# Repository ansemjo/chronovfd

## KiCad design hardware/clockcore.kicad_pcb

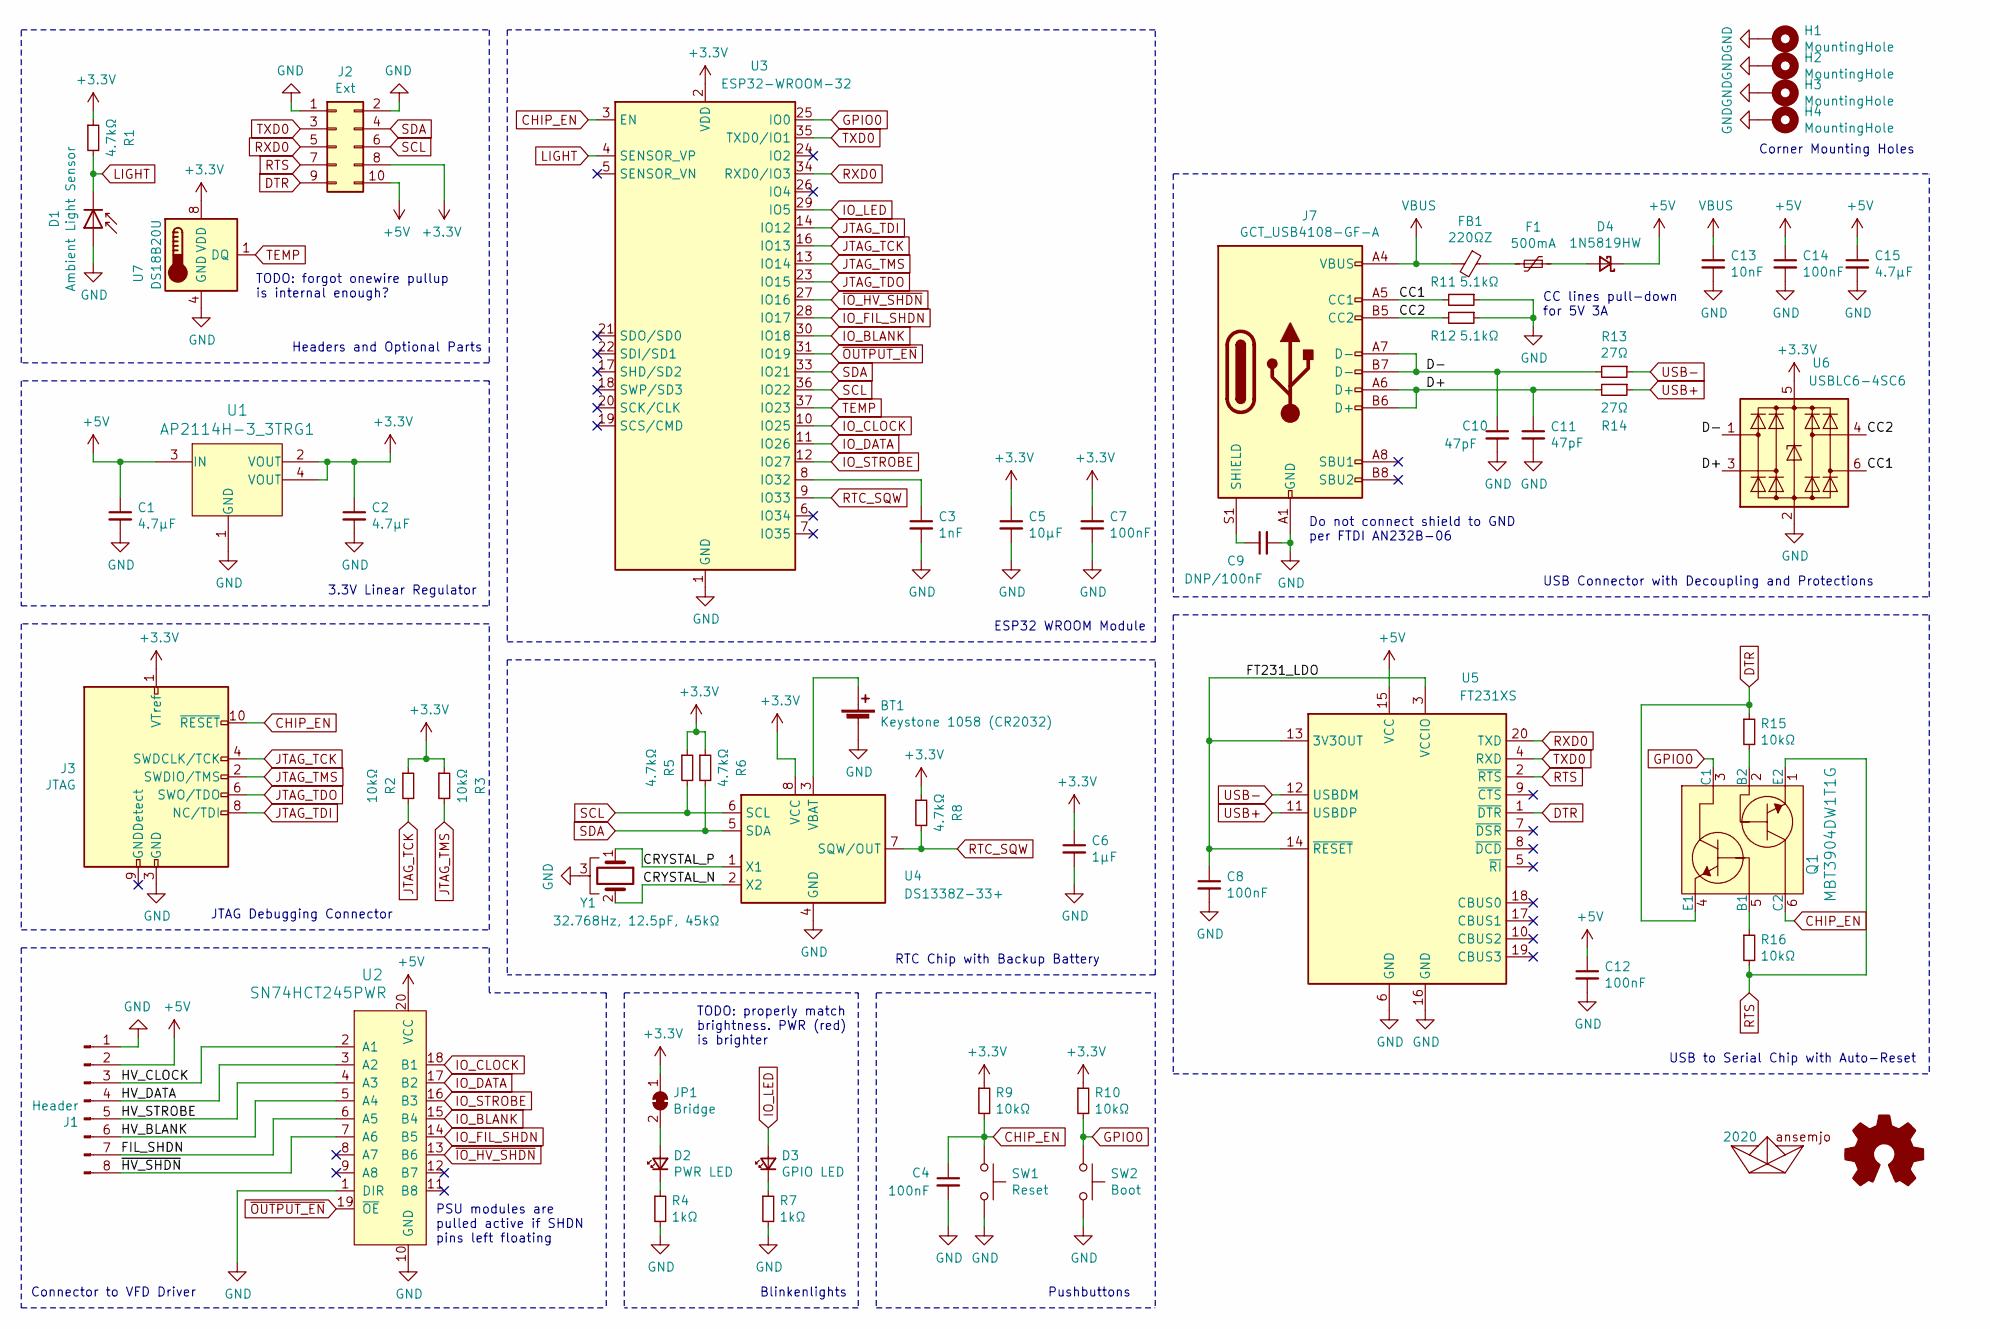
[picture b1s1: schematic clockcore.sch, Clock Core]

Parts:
A1: 2020; AHOI
A2: Logo_Open_Hardware_Small; OSHW-Symbol_6.7x6mm_SilkScreen
BT1: Keystone 1058 (CR2032); BatteryHolder_Keystone_1058_1x2032; MPN 1058; Digi-Key_PN 36-1058-ND
C1, C2, C15: 4.7µF; C_0805_2012Metric_Pad1.15x1.40mm_HandSolder; MPN CL21A475KAQNNNE; Digi-Key_PN 1276-1244-1-ND
C3: 1nF; C_0805_2012Metric_Pad1.15x1.40mm_HandSolder; MPN CL21B102KBANNNC; Digi-Key_PN 1276-1020-1-ND
C4, C7, C8, C12, C14: 100nF; C_0805_2012Metric_Pad1.15x1.40mm_HandSolder; MPN CL21B104KACNNNC; Digi-Key_PN 1276-1099-1-ND
C5: 10µF; C_0805_2012Metric_Pad1.15x1.40mm_HandSolder; MPN CL21A106KOQNNNE; Digi-Key_PN 1276-1096-1-ND
C6: 1µF; C_0805_2012Metric_Pad1.15x1.40mm_HandSolder; MPN CL21B105KAFNNNG; Digi-Key_PN 1276-6469-1-ND
C9: DNP/100nF; C_0805_2012Metric_Pad1.15x1.40mm_HandSolder; MPN CL21B104KACNNNC; Digi-Key_PN 1276-1099-1-ND
C10, C11: 47pF; C_0805_2012Metric_Pad1.15x1.40mm_HandSolder; MPN CC0805JRNPO9BN470; Digi-Key_PN 311-1107-1-ND
C13: 10nF; C_0805_2012Metric_Pad1.15x1.40mm_HandSolder; MPN CC0805KRX7R9BB103; Digi-Key_PN 311-1136-1-ND
D1: Ambient Light Sensor; D_1206_3216Metric_Castellated; MPN VEMD1060X01; Digi-Key_PN VEMD1060X01CT-ND
D2: PWR LED; LED_0805_2012Metric_Pad1.15x1.40mm_HandSolder; MPN 150080SS75000; Digi-Key_PN 732-4985-1-ND
D3: GPIO LED; LED_0805_2012Metric_Pad1.15x1.40mm_HandSolder; MPN 150080VS75000; Digi-Key_PN 732-4986-1-ND
D4: 1N5819HW; D_SOD-123; MPN 1N5819HW-7-F; Digi-Key_PN 1N5819HW-FDICT-ND
F1: 500mA; Fuse_1206_3216Metric_Pad1.42x1.75mm_HandSolder; MPN 0ZCJ0050FF2G; Digi-Key_PN 507-1802-1-ND
FB1: 220ΩZ; L_0805_2012Metric_Pad1.15x1.40mm_HandSolder; MPN BLM21PG221SZ1D; Digi-Key_PN 490-16661-1-ND
H1, H2, H3, H4: MountingHole; MountingHole_2.7mm_M2.5_Pad
J1: Header; PinSocket_1x08_P2.54mm_Vertical; MPN PPTC081LFBN-RC; Digi-Key_PN S7006-ND
J2: Ext; PinHeader_2x05_P2.54mm_Vertical; MPN PRPC040DAAN-RC; Digi-Key_PN S2011EC-40-ND
J3: JTAG; JTAG_2x05_P1.27mm_Vertical_SMD; MPN 20021121-00010C4LF; Digi-Key_PN 609-3695-6-ND
J7: GCT_USB4108-GF-A; USB_C_Receptacle_HRO_TYPE-C-31-M-12; MPN USB4105-GF-A; Digi-Key_PN 2073-USB4105-GF-ACT-ND
JP1: Bridge; SolderJumper-2_P1.3mm_Bridged_RoundedPad1.0x1.5mm
Q1: MBT3904DW1T1G; SOT-363; MPN MBT3904DW1T1G; Digi-Key_PN MBT3904DW1T1GOSCT-ND
R1, R5, R6, R8: 4.7kΩ; R_0805_2012Metric_Pad1.15x1.40mm_HandSolder; MPN RC0805FR-074K7L; Digi-Key_PN 311-4.70KCRCT-ND
R2, R3, R9, R10, R15, R16: 10kΩ; R_0805_2012Metric_Pad1.15x1.40mm_HandSolder; MPN RC0805FR-0710KL; Digi-Key_PN 311-10.0KCRCT-ND
R4, R7: 1kΩ; R_0805_2012Metric_Pad1.15x1.40mm_HandSolder; MPN RC0805FR-071KL; Digi-Key_PN 311-1.00KCRCT-ND
R11, R12: 5.1kΩ; R_0805_2012Metric_Pad1.15x1.40mm_HandSolder; MPN RC0805JR-075K1L; Digi-Key_PN 311-5.1KARCT-ND
R13, R14: 27Ω; R_0805_2012Metric_Pad1.15x1.40mm_HandSolder; MPN RC0805FR-0727RL; Digi-Key_PN 311-27.0CRCT-ND
SW1: Reset; SW_PTS526_SM08_SMTR2_LFS; MPN PTS526 SK15 SMTR2 LFS; Digi-Key_PN CKN12221-1-ND
SW2: Boot; SW_PTS526_SM08_SMTR2_LFS; MPN PTS526 SK15 SMTR2 LFS; Digi-Key_PN CKN12221-1-ND
U1: AP2114H-3_3TRG1; SOT-223; MPN AP2114H-3.3TRG1; Digi-Key_PN AP2114H-3.3TRG1DICT-ND
U2: ‎SN74HCT245PWR‎; TSSOP-20_4.4x6.5mm_P0.65mm; MPN SN74HCT245PWR; Digi-Key_PN 296-8404-1-ND
U3: ESP32-WROOM-32; MPN ESP32-WROOM-32E (8MB); Digi-Key_PN 1965-ESP32-WROOM-32E(8MBFLASH)CT-ND
U4: DS1338Z-33+; SOIC-8_3.9x4.9mm_P1.27mm; MPN DS1338Z-33+T&R; Digi-Key_PN DS1338Z-33+T&RCT-ND
U5: FT231XS; SSOP-20_3.9x8.7mm_P0.635mm; MPN FT231XS-R; Digi-Key_PN 768-1129-1-ND
U6: USBLC6-4SC6; SOT-23-6; MPN USBLC6-4SC6; Digi-Key_PN 497-4492-1-ND
U7: DS18B20U; MSOP-8_3x3mm_P0.65mm; MPN DS18B20U+T&R; Digi-Key_PN DS18B20U+T&RCT-ND
Y1: 32.768Hz, 12.5pF, 45kΩ; Crystal_SMD_MicroCrystal_MS1V-T1K; MPN ECS-.327-12.5-13FLX-C; Digi-Key_PN XC1911CT-ND

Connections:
+3V3: C2.1, C5.1, C6.1, C7.1, J2.8, J3.1 (VTref), JP1.1 (A), R1.1, R2.1, R3.1, R5.1, R6.1, R8.1, R9.1, R10.1, U1.2 (VOUT), U1.4 (VOUT), U3.2 (VDD), U4.8 (VCC), U6.5 (VBUS), U7.8 (VDD)
+5V: C1.1, C12.1, C14.1, C15.1, D4.1 (K), J1.2, J2.10, U1.3 (IN), U2.20 (VCC), U5.15 (VCC)
/CC1: J7.A5 (CC1), R11.2, U6.6 (I/O4)
/CC2: J7.B5 (CC2), R12.2, U6.4 (I/O3)
/CRYSTAL_N: U4.2 (X2), Y1.2
/CRYSTAL_P: U4.1 (X1), Y1.1
/D+: C11.1, J7.A6 (D+), J7.B6 (D+), R14.2, U6.3 (I/O2)
/D-: C10.1, J7.A7 (D-), J7.B7 (D-), R13.2, U6.1 (I/O1)
/FIL_SHDN: J1.7, U2.6 (A5)
/FT231_LDO: C8.1, U5.3 (VCCIO), U5.13 (3V3OUT), U5.14 (~RESET)
/HV_BLANK: J1.6, U2.5 (A4)
/HV_CLOCK: J1.3, U2.2 (A1)
/HV_DATA: J1.4, U2.3 (A2)
/HV_STROBE: J1.5, U2.4 (A3)
/~HV_SHDN~: J1.8, U2.7 (A6)
CHIP_EN: C4.1, J3.10 (~RESET~), Q1.6 (C2), R9.2, SW1.1, U3.3 (EN)
DTR: J2.9, Q1.4 (E1), R15.1, U5.1 (~DTR)
GND: BT1.2 (-), C1.2, C2.2, C3.2, C4.2, C5.2, C6.2, C7.2, C8.2, C9.2, C10.2, C11.2, C12.2, C13.2, C14.2, C15.2, D1.2 (A), H1.1, H2.1, H3.1, H4.1, J1.1, J2.1, J2.2, J3.3 (GND), J3.5 (GND), J7.A1 (GND), J7.A12 (GND), J7.B1 (GND), J7.B12 (GND), R4.2, R7.2, R11.1, R12.1, SW1.2, SW2.2, U1.1 (GND), U2.1 (DIR), U2.10 (GND), U3.1 (GND), U3.15 (GND), U3.38 (GND), U3.39 (GND), U4.4 (GND), U5.6 (GND), U5.16 (GND), U6.2 (GND), U7.4 (GND), Y1.3
GPIO0: Q1.3 (C1), R10.2, SW2.1, U3.25 (IO0)
IO_BLANK: U2.15 (B4), U3.30 (IO18)
IO_CLOCK: U2.18 (B1), U3.10 (IO25)
IO_DATA: U2.17 (B2), U3.11 (IO26)
IO_FIL_SHDN: U2.14 (B5), U3.28 (IO17)
IO_LED: D3.2 (A), U3.29 (IO5)
IO_STROBE: U2.16 (B3), U3.12 (IO27)
JTAG_TCK: J3.4 (SWDCLK/TCK), R2.2, U3.16 (IO13)
JTAG_TDI: J3.8 (NC/TDI), U3.14 (IO12)
JTAG_TDO: J3.6 (SWO/TDO), U3.23 (IO15)
JTAG_TMS: J3.2 (SWDIO/TMS), R3.2, U3.13 (IO14)
LIGHT: D1.1 (K), R1.2, U3.4 (SENSOR_VP)
unnamed: BT1.1 (+), U4.3 (VBAT)
unnamed: C3.1, U3.8 (IO32)
unnamed: C9.1, J7.S1 (SHIELD)
unnamed: D2.1 (K), R4.1
unnamed: D2.2 (A), JP1.2 (B)
unnamed: D3.1 (K), R7.1
unnamed: D4.2 (A), F1.1
unnamed: F1.2, FB1.1
unnamed: Q1.2 (B2), R15.2
unnamed: Q1.5 (B1), R16.1
RTC_SQW: R8.2, U3.9 (IO33), U4.7 (SQW/OUT)
RTS: J2.7, Q1.1 (E2), R16.2, U5.2 (~RTS)
RXD0: J2.5, U3.34 (RXD0/IO3), U5.20 (TXD)
SCL: J2.6, R5.2, U3.36 (IO22), U4.6 (SCL)
SDA: J2.4, R6.2, U3.33 (IO21), U4.5 (SDA)
TEMP: U3.37 (IO23), U7.1 (DQ)
TXD0: J2.3, U3.35 (TXD0/IO1), U5.4 (RXD)
USB+: R14.1, U5.11 (USBDP)
USB-: R13.1, U5.12 (USBDM)
VBUS: C13.1, FB1.2, J7.A4 (VBUS), J7.A9 (VBUS), J7.B4 (VBUS), J7.B9 (VBUS)
~IO_HV_SHDN~: U2.13 (B6), U3.27 (IO16)
~OUTPUT_EN~: U2.19 (~OE), U3.31 (IO19)

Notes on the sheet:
CC lines pull-down for 5V 3A
PSU modules are pulled active if SHDN pins left floating
RTC Chip with Backup Battery
USB Connector with Decoupling and Protections
USB to Serial Chip with Auto-Reset
Connector to VFD Driver
Blinkenlights
Pushbuttons
Corner Mounting Holes
Do not connect shield to GND per FTDI AN232B-06
JTAG Debugging Connector
3.3V Linear Regulator
Headers and Optional Parts
ESP32 WROOM Module
TODO: forgot onewire pullup is internal enough?
TODO: properly match brightness. PWR (red) is brighter

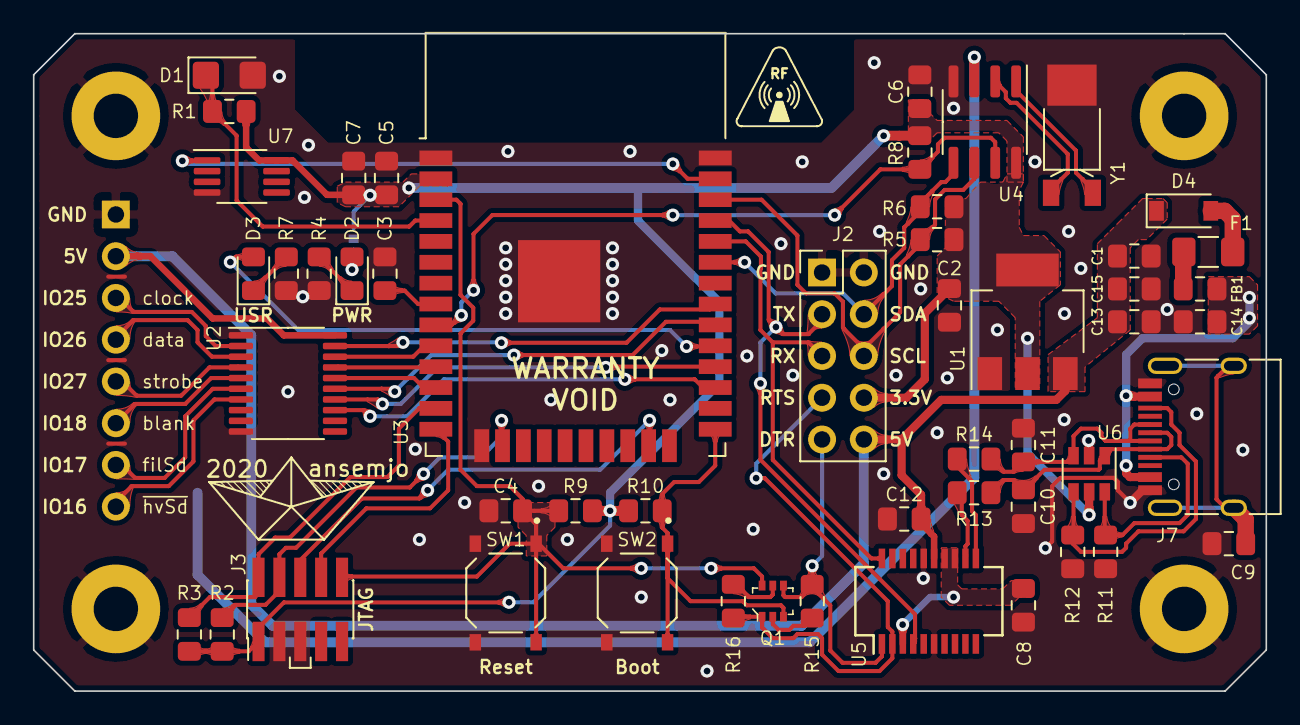
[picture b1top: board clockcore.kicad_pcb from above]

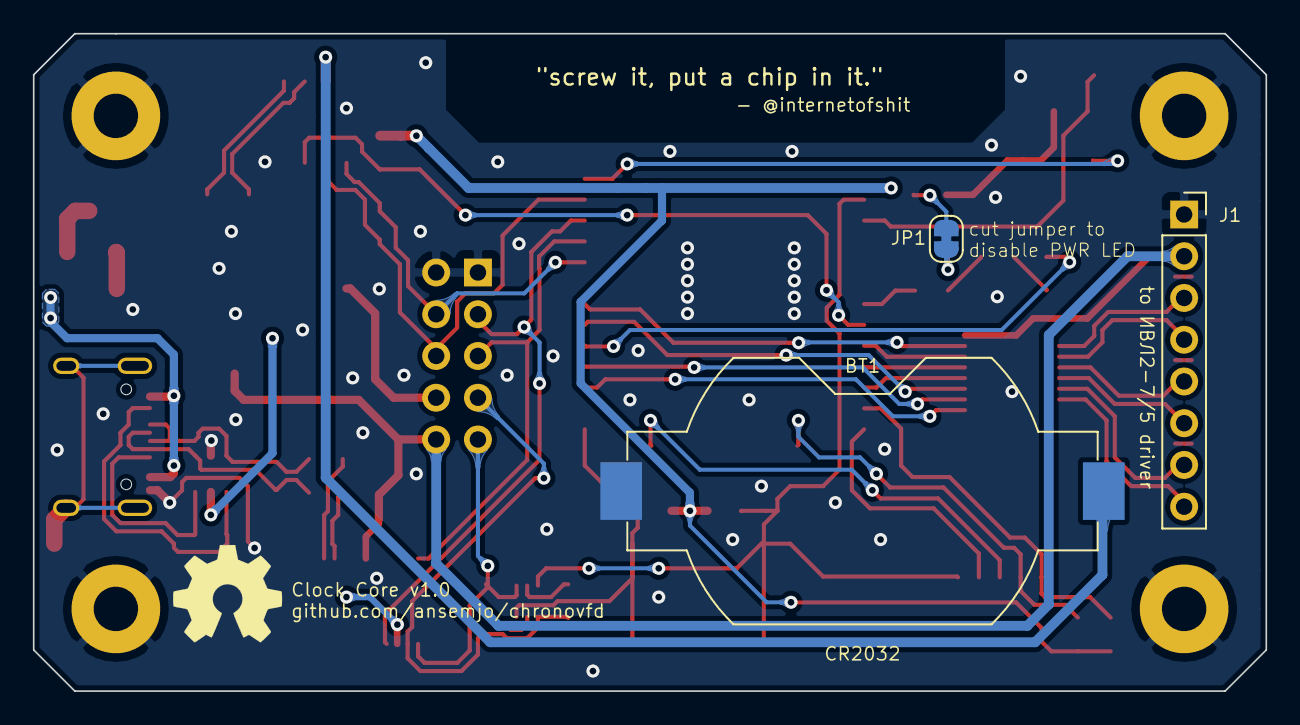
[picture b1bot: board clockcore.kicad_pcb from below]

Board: 2 copper layers, 75.0 x 40.0 mm, 60 parts (4 on the bottom side), 52 nets.

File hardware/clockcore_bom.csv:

References,Value,Footprint,Quantity,Digi-Key PN,Manufacturer,MPN
BT1,Keystone 1058 (CR2032),BatteryHolder_Keystone_1058_1x2032,1,36-1058-ND,Keystone,1058
C4 C7 C8 C12 C14,100nF,C_0805_2012Metric_Pad1.15x1.40mm_HandSolder,5,1276-1099-1-ND,Samsung,CL21B104KACNNNC
C13,10nF,C_0805_2012Metric_Pad1.15x1.40mm_HandSolder,1,311-1136-1-ND,Yageo,CC0805KRX7R9BB103
C5,10µF,C_0805_2012Metric_Pad1.15x1.40mm_HandSolder,1,1276-1096-1-ND,Samsung,CL21A106KOQNNNE
C3,1nF,C_0805_2012Metric_Pad1.15x1.40mm_HandSolder,1,1276-1020-1-ND,Samsung,CL21B102KBANNNC
C6,1µF,C_0805_2012Metric_Pad1.15x1.40mm_HandSolder,1,1276-6469-1-ND,Samsung,CL21B105KAFNNNG
C1 C2 C15,4.7µF,C_0805_2012Metric_Pad1.15x1.40mm_HandSolder,3,1276-1244-1-ND,Samsung,CL21A475KAQNNNE
C10 C11,47pF,C_0805_2012Metric_Pad1.15x1.40mm_HandSolder,2,311-1107-1-ND,Yageo,CC0805JRNPO9BN470
C9,DNP/100nF,C_0805_2012Metric_Pad1.15x1.40mm_HandSolder,1,1276-1099-1-ND,Samsung,CL21B104KACNNNC
D4,1N5819HW,D_SOD-123,1,1N5819HW-FDICT-ND,Diodes Inc.,1N5819HW-7-F
D1,Ambient Light Sensor,D_1206_3216Metric_Castellated,1,VEMD1060X01CT-ND,Vishay,VEMD1060X01
D3,GPIO LED,LED_0805_2012Metric_Pad1.15x1.40mm_HandSolder,1,732-4986-1-ND,Würth,150080VS75000
D2,PWR LED,LED_0805_2012Metric_Pad1.15x1.40mm_HandSolder,1,732-4985-1-ND,Würth,150080SS75000
F1,500mA,Fuse_1206_3216Metric_Pad1.42x1.75mm_HandSolder,1,507-1802-1-ND,Bel Fuse,0ZCJ0050FF2G
FB1,220ΩZ,L_0805_2012Metric_Pad1.15x1.40mm_HandSolder,1,490-16661-1-ND,Murata,BLM21PG221SZ1D
J2,Ext,PinHeader_2x05_P2.54mm_Vertical,1,S2011EC-40-ND,Sullins,PRPC040DAAN-RC
J7,GCT_USB4108-GF-A,USB_C_Receptacle_HRO_TYPE-C-31-M-12,1,2073-USB4105-GF-ACT-ND,GCT,USB4105-GF-A
J1,Header,PinSocket_1x08_P2.54mm_Vertical,1,S7006-ND,Sullins,PPTC081LFBN-RC
J3,JTAG,JTAG_2x05_P1.27mm_Vertical_SMD,1,609-3695-6-ND,Amphenol,20021121-00010C4LF
Q1,MBT3904DW1T1G,SOT-363,1,MBT3904DW1T1GOSCT-ND,ON Semiconductor,MBT3904DW1T1G
R2 R3 R9 R10 R15 R16,10kΩ,R_0805_2012Metric_Pad1.15x1.40mm_HandSolder,6,311-10.0KCRCT-ND,Yageo,RC0805FR-0710KL
R4 R7,1kΩ,R_0805_2012Metric_Pad1.15x1.40mm_HandSolder,2,311-1.00KCRCT-ND,Yageo,RC0805FR-071KL
R13 R14,27Ω,R_0805_2012Metric_Pad1.15x1.40mm_HandSolder,2,311-27.0CRCT-ND,Yageo,RC0805FR-0727RL
R1 R5 R6 R8,4.7kΩ,R_0805_2012Metric_Pad1.15x1.40mm_HandSolder,4,311-4.70KCRCT-ND,Yageo,RC0805FR-074K7L
R11 R12,5.1kΩ,R_0805_2012Metric_Pad1.15x1.40mm_HandSolder,2,311-5.1KARCT-ND,Yageo,RC0805JR-075K1L
SW2,Boot,SW_PTS526_SM08_SMTR2_LFS,1,CKN12221-1-ND,C&K,PTS526 SK15 SMTR2 LFS
SW1,Reset,SW_PTS526_SM08_SMTR2_LFS,1,CKN12221-1-ND,C&K,PTS526 SK15 SMTR2 LFS
U1,AP2114H-3_3TRG1,SOT-223,1,AP2114H-3.3TRG1DICT-ND,Diodes Inc.,AP2114H-3.3TRG1
U4,DS1338Z-33+,SOIC-8_3.9x4.9mm_P1.27mm,1,DS1338Z-33+T&RCT-ND,Maxim,DS1338Z-33+T&R
U7,DS18B20U,MSOP-8_3x3mm_P0.65mm,1,DS18B20U+T&RCT-ND,Maxim,DS18B20U+T&R
U3,ESP32-WROOM-32,ESP32-WROOM-32,1,1965-ESP32-WROOM-32E(8MBFLASH)CT-ND,Espressif,ESP32-WROOM-32E (8MB)
U5,FT231XS,SSOP-20_3.9x8.7mm_P0.635mm,1,768-1129-1-ND,FTDI,FT231XS-R
U6,USBLC6-4SC6,SOT-23-6,1,497-4492-1-ND,ST Microelectronic,USBLC6-4SC6
U2,‎SN74HCT245PWR‎,TSSOP-20_4.4x6.5mm_P0.65mm,1,296-8404-1-ND,Texas Instruments,SN74HCT245PWR
Y1,"32.768Hz, 12.5pF, 45kΩ",Crystal_SMD_MicroCrystal_MS1V-T1K,1,XC1911CT-ND,ECS Inc.,ECS-.327-12.5-13FLX-C

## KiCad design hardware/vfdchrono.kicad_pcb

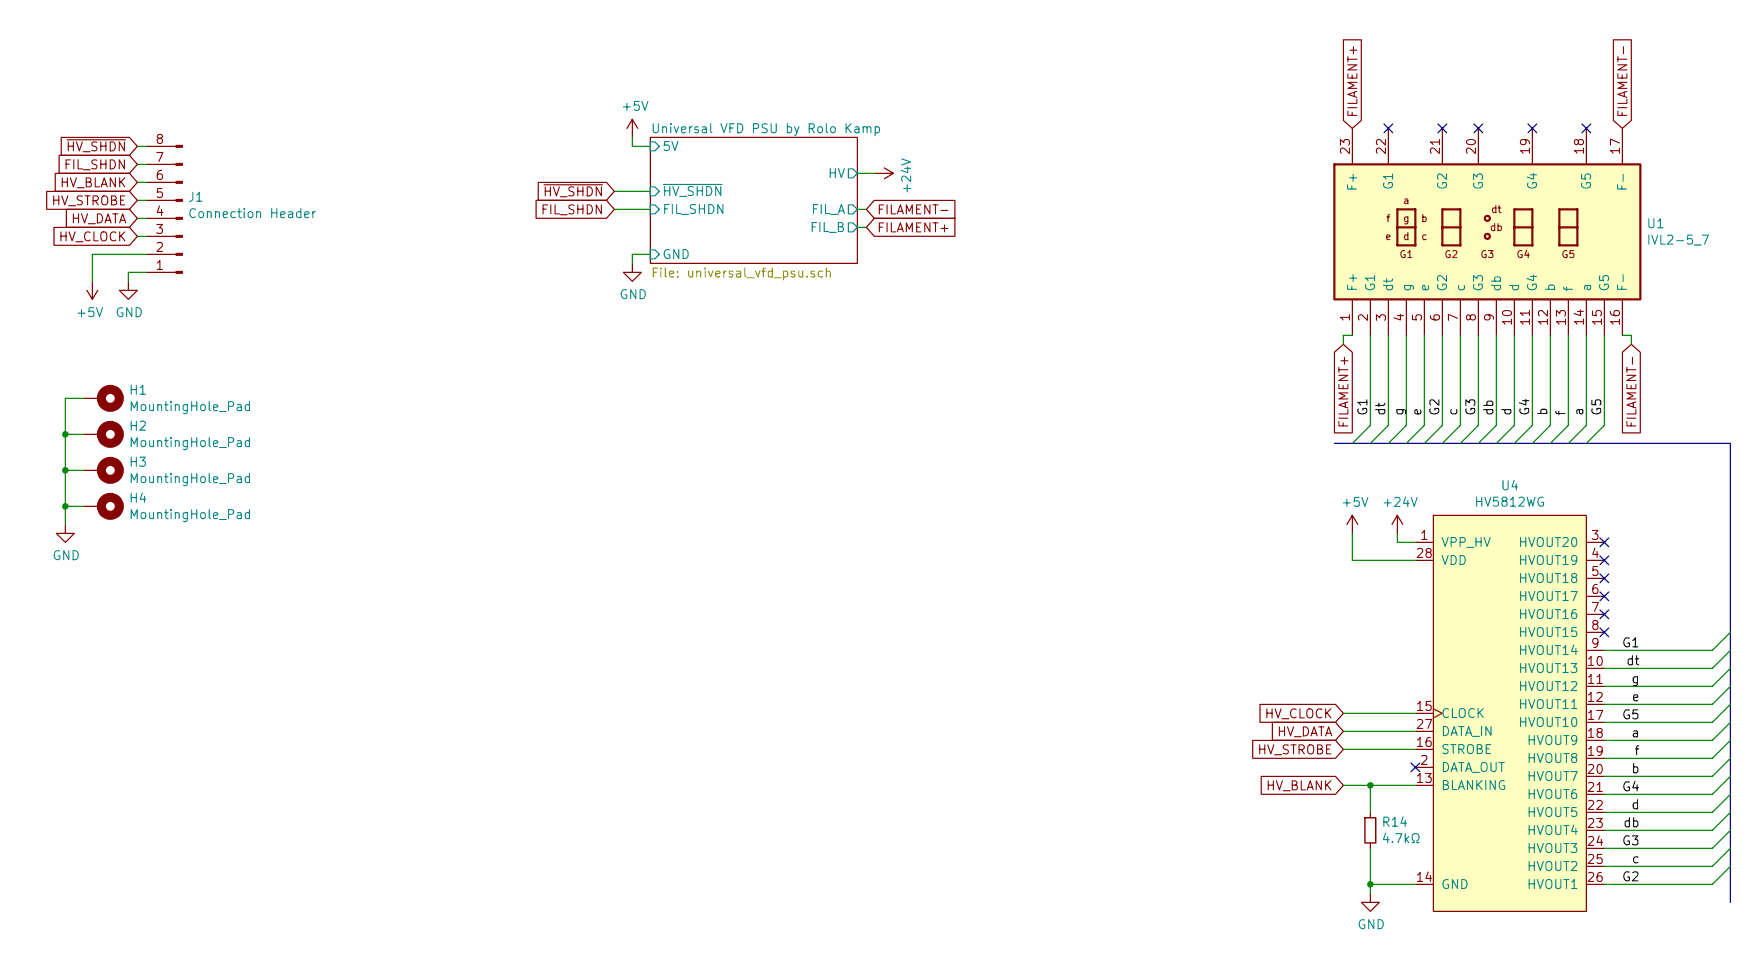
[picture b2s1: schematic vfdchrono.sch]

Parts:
H1, H2, H3, H4: MountingHole_Pad; MountingHole_2.7mm_M2.5_Pad
J1: Connection Header; PinHeader_1x08_P2.54mm_Vertical
R14: 4.7kΩ; R_0805_2012Metric_Pad1.15x1.40mm_HandSolder
U1: IVL2-5_7; IVL2-7_5
U4: HV5812WG; SOIC-28W_7.5x17.9mm_P1.27mm

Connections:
+5V: J1.2, U4.28 (VDD); also elsewhere on the board
+24V: U4.1 (VPP_HV); also elsewhere on the board
/G1: U1.2 (G1), U4.9 (HVOUT14)
/G2: U1.6 (G2), U4.26 (HVOUT1)
/G3: U1.8 (G3), U4.24 (HVOUT3)
/G4: U1.11 (G4), U4.21 (HVOUT6)
/G5: U1.15 (G5), U4.17 (HVOUT10)
/a: U1.14 (a), U4.18 (HVOUT9)
/b: U1.12 (b), U4.20 (HVOUT7)
/c: U1.7 (c), U4.25 (HVOUT2)
/d: U1.10 (d), U4.22 (HVOUT5)
/db: U1.9 (db), U4.23 (HVOUT4)
/dt: U1.3 (dt), U4.10 (HVOUT13)
/e: U1.5 (e), U4.12 (HVOUT11)
/f: U1.13 (f), U4.19 (HVOUT8)
/g: U1.4 (g), U4.11 (HVOUT12)
FILAMENT+: U1.1 (F+), U1.23 (F+); also elsewhere on the board
FILAMENT-: U1.16 (F-), U1.17 (F-); also elsewhere on the board
FIL_SHDN: J1.7; also elsewhere on the board
GND: H1.1, H2.1, H3.1, H4.1, J1.1, R14.2, U4.14 (GND); also elsewhere on the board
HV_BLANK: J1.6, R14.1, U4.13 (BLANKING)
HV_CLOCK: J1.3, U4.15 (CLOCK)
HV_DATA: J1.4, U4.27 (DATA_IN)
HV_STROBE: J1.5, U4.16 (STROBE)
~HV_SHDN~: J1.8; also elsewhere on the board

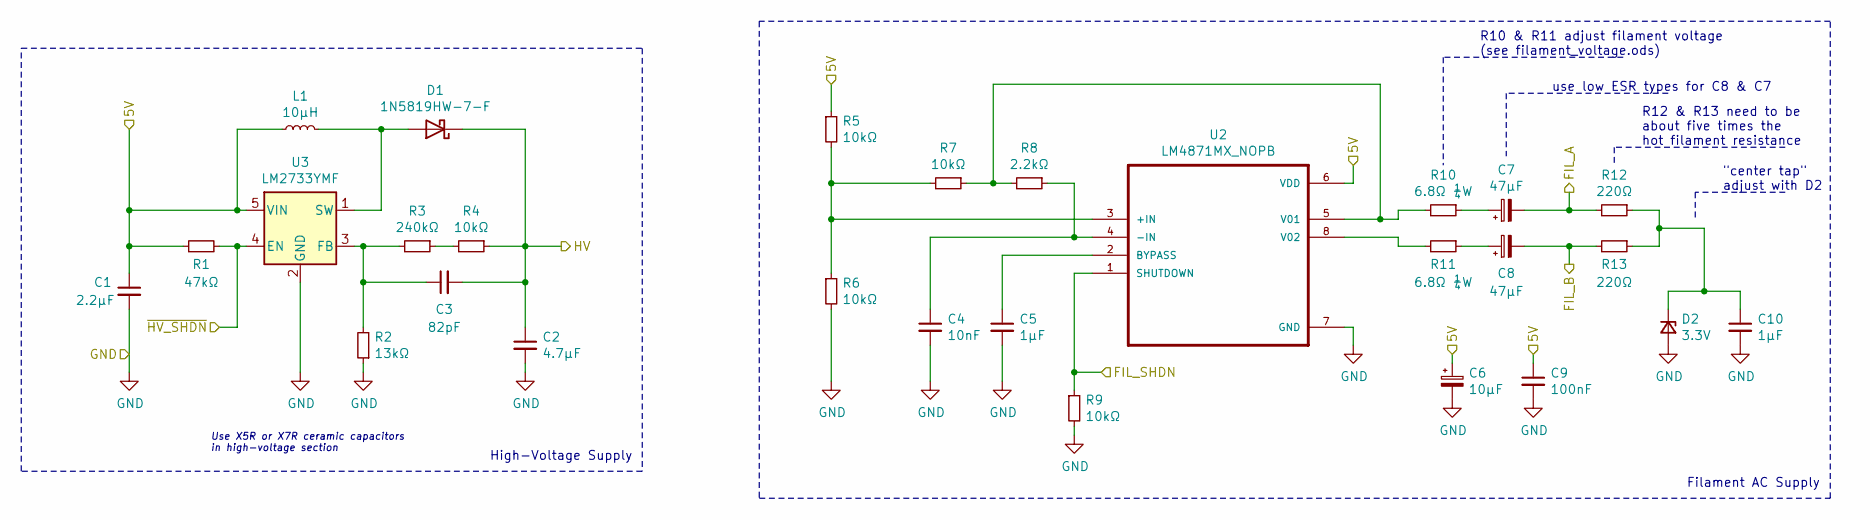
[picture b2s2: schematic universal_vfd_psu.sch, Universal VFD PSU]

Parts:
C1: 2.2µF; C_0805_2012Metric_Pad1.15x1.40mm_HandSolder
C2: 4.7µF; C_0805_2012Metric_Pad1.15x1.40mm_HandSolder
C3: 82pF; C_0805_2012Metric_Pad1.15x1.40mm_HandSolder
C4: 10nF; C_0805_2012Metric_Pad1.15x1.40mm_HandSolder
C5, C10: 1µF; C_0805_2012Metric_Pad1.15x1.40mm_HandSolder
C6: 10µF; CP_Elec_4x5.4
C7, C8: 47µF; CP_Elec_6.3x5.9
C9: 100nF; C_0805_2012Metric_Pad1.15x1.40mm_HandSolder
D1: 1N5819HW-7-F; D_SOD-123
D2: 3.3V; D_SOD-123
L1: 10µH; L_1210_3225Metric_Pad1.42x2.65mm_HandSolder
R1: 47kΩ; R_0805_2012Metric_Pad1.15x1.40mm_HandSolder
R2: 13kΩ; R_0805_2012Metric_Pad1.15x1.40mm_HandSolder
R3: 240kΩ; R_0805_2012Metric_Pad1.15x1.40mm_HandSolder
R4, R5, R6, R7, R9: 10kΩ; R_0805_2012Metric_Pad1.15x1.40mm_HandSolder
R8: 2.2kΩ; R_0805_2012Metric_Pad1.15x1.40mm_HandSolder
R10, R11: 6.8Ω ¼W; R_1206_3216Metric_Pad1.42x1.75mm_HandSolder
R12, R13: 220Ω; R_0805_2012Metric_Pad1.15x1.40mm_HandSolder
U2: LM4871MX_NOPB; SOIC-8_3.9x4.9mm_P1.27mm
U3: LM2733YMF; SOT-23-5

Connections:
+5V: C1.1, C6.1, C9.1, L1.1, R1.1, R5.1, U2.6 (VDD), U3.5 (VIN); also elsewhere on the board
+24V: C2.1, C3.2, D1.1 (K), R4.1; also elsewhere on the board
FILAMENT+: C8.2, R13.2; also elsewhere on the board
FILAMENT-: C7.2, R12.2; also elsewhere on the board
FIL_SHDN: R9.1, U2.1 (SHUTDOWN); also elsewhere on the board
GND: C1.2, C2.2, C4.2, C5.2, C6.2, C9.2, C10.2, D2.2 (A), R2.1, R6.2, R9.2, U2.7 (GND), U3.2 (GND); also elsewhere on the board
unnamed: C3.1, R2.2, R3.2, U3.3 (FB)
unnamed: C4.1, R8.1, U2.4 (-IN)
unnamed: C5.1, U2.2 (BYPASS)
unnamed: C7.1, R10.1
unnamed: C8.1, R11.1
unnamed: C10.1, D2.1 (K), R12.1, R13.1
unnamed: D1.2 (A), L1.2, U3.1 (SW)
unnamed: R3.1, R4.2
unnamed: R5.2, R6.1, R7.2, U2.3 (+IN)
unnamed: R7.1, R8.2, R10.2, U2.5 (V01)
unnamed: R11.2, U2.8 (V02)
~HV_SHDN~: R1.2, U3.4 (EN); also elsewhere on the board

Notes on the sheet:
High-Voltage Supply
Filament AC Supply
use low ESR types for C8 & C7
R10 & R11 adjust filament voltage (see filament_voltage.ods)
"center tap" adjust with D2
Use X5R or X7R ceramic capacitors in high-voltage section
R12 & R13 need to be about five times the hot filament resistance

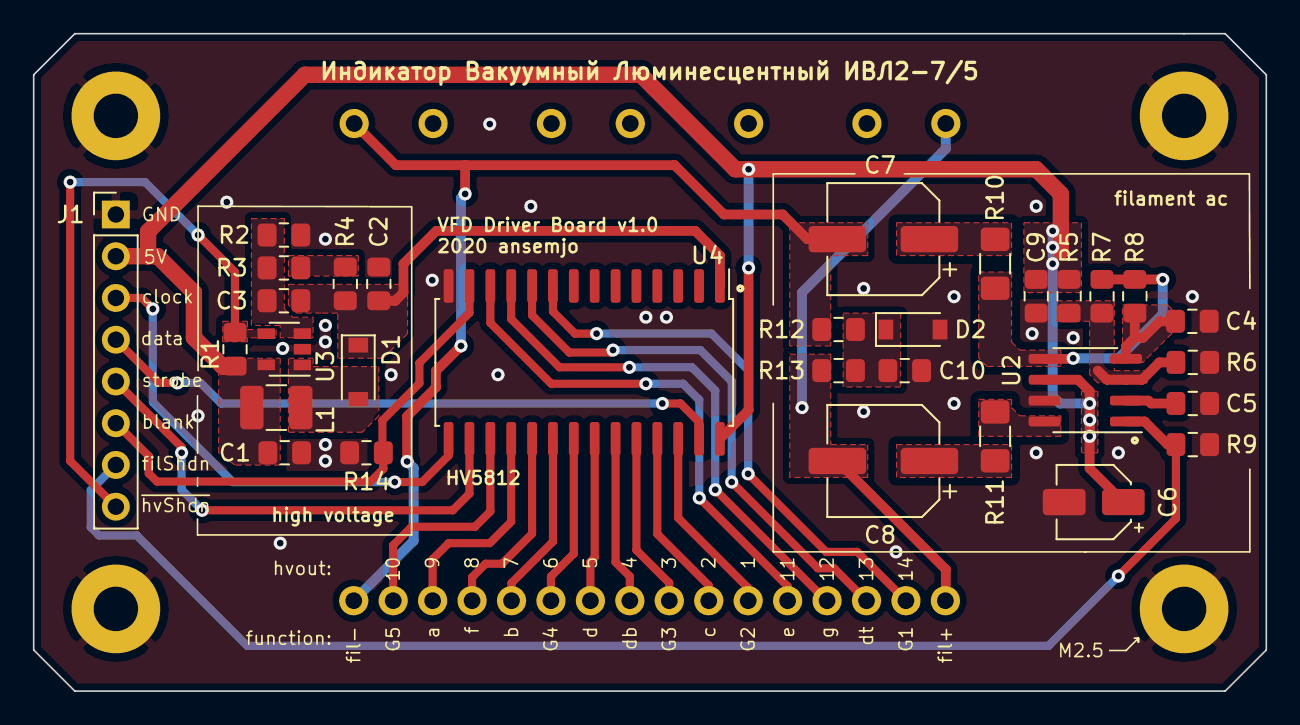
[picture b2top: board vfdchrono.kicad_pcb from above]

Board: 2 copper layers, 75.0 x 40.0 mm, 36 parts (1 on the bottom side), 36 nets.

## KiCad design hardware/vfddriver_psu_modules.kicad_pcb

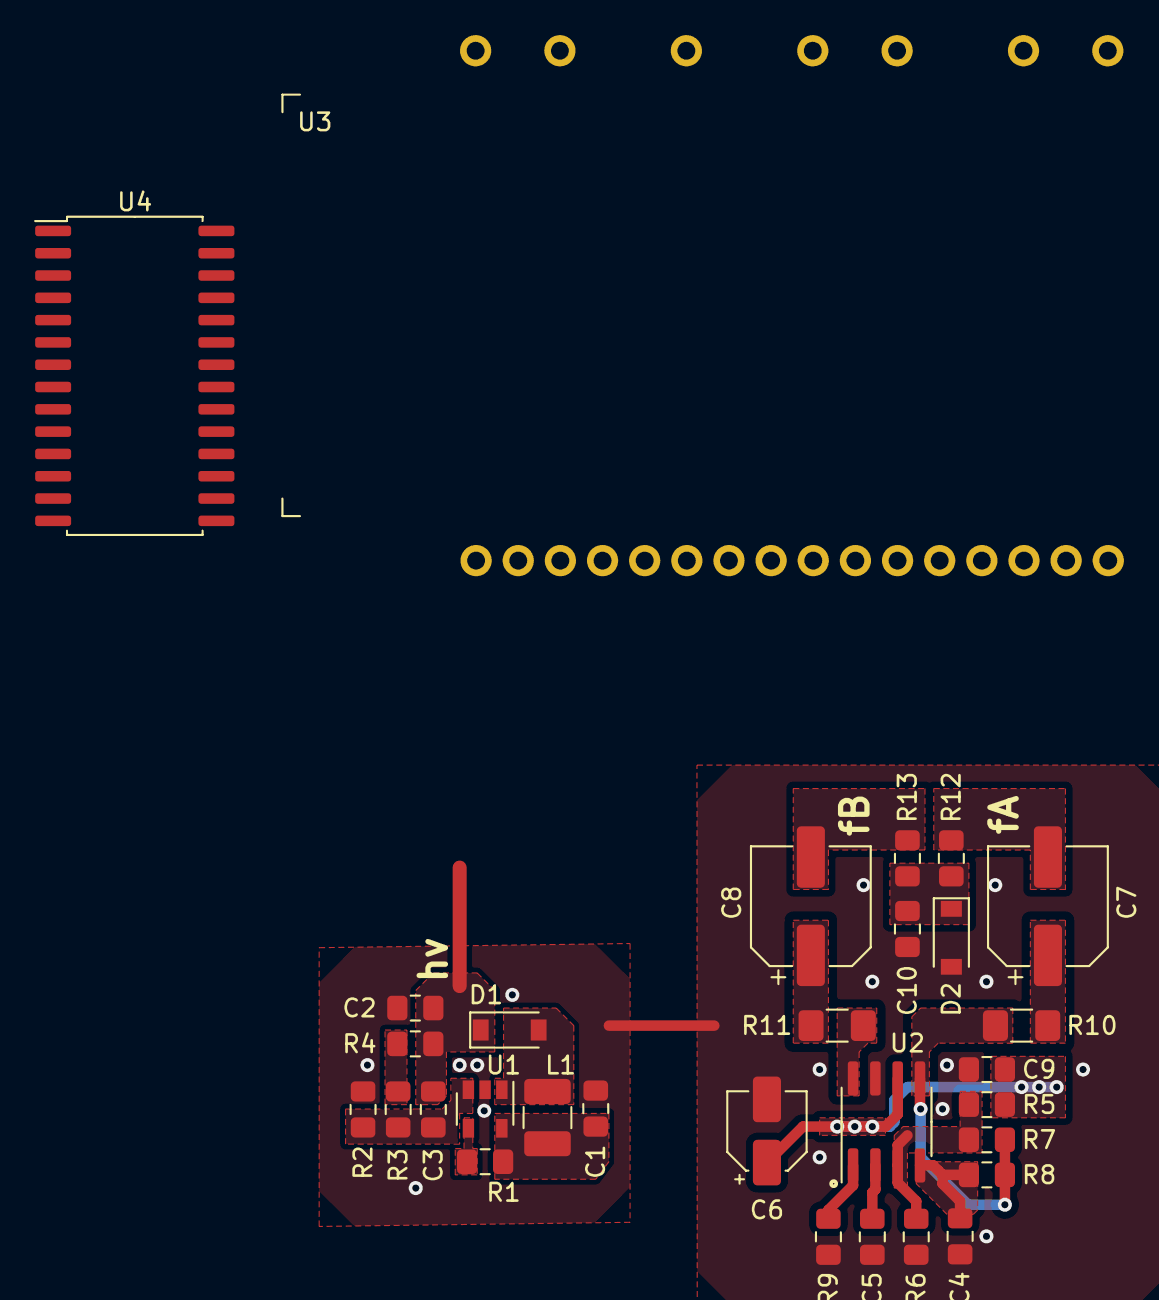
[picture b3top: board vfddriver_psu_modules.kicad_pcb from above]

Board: 2 copper layers, 30 parts (0 on the bottom side), 32 nets.

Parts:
C1: 2.2µF; C_0805_2012Metric_Pad1.15x1.40mm_HandSolder
C2: 4.7µF; C_0805_2012Metric_Pad1.15x1.40mm_HandSolder
C3: 82pF; C_0805_2012Metric_Pad1.15x1.40mm_HandSolder
C4: 10nF; C_0805_2012Metric_Pad1.15x1.40mm_HandSolder
C5, C10: 1µF; C_0805_2012Metric_Pad1.15x1.40mm_HandSolder
C6: 10µF; CP_Elec_4x5.4
C7, C8: 47µF; CP_Elec_6.3x5.9
C9: 100nF; C_0805_2012Metric_Pad1.15x1.40mm_HandSolder
D1: 1N5819HW-7-F; D_SOD-123
D2: 3.3V; D_SOD-123
L1: 10µH; L_1210_3225Metric_Pad1.42x2.65mm_HandSolder
R1: 47kΩ; R_0805_2012Metric_Pad1.15x1.40mm_HandSolder
R2: 13kΩ; R_0805_2012Metric_Pad1.15x1.40mm_HandSolder
R3: 240kΩ; R_0805_2012Metric_Pad1.15x1.40mm_HandSolder
R4, R5, R6, R7, R9: 10kΩ; R_0805_2012Metric_Pad1.15x1.40mm_HandSolder
R8: 2.2kΩ; R_0805_2012Metric_Pad1.15x1.40mm_HandSolder
R10, R11: 10Ω; R_1206_3216Metric_Pad1.42x1.75mm_HandSolder
R12, R13: 220Ω; R_0805_2012Metric_Pad1.15x1.40mm_HandSolder
U1: LM2733YMF; SOT-23-5
U2: LM4871MX_NOPB; SOIC-8_3.9x4.9mm_P1.27mm
U3: IVL2-5_7; IVL2-7_5
U4: HV5812WG; SOIC-28W_7.5x17.9mm_P1.27mm

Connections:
+5V: C1.1, C6.1, C9.1, L1.1, R1.1, R5.1, U1.5, U2.6, U4.28
+24V: C2.1, C3.2, D1.1, R4.1, U4.1
/G1: U3.2, U3.22, U4.9
/G2: U3.6, U3.21, U4.17
/G3: U3.8, U3.20, U4.19
/G4: U3.11, U3.19, U4.22
/G5: U3.15, U3.18, U4.26
/Universal VFD PSU by Rolo Kamp/FIL_SHDN: R9.1, U2.1
/Universal VFD PSU by Rolo Kamp/~HV_SHDN~: R1.2, U1.4
/a: U3.14, U4.25
/b: U3.12, U4.23
/c: U3.7, U4.18
/d: U3.10, U4.21
/db: U3.9, U4.20
/dt: U3.3, U4.10
/e: U3.5, U4.12
/f: U3.13, U4.24
/g: U3.4, U4.11
FILAMENT+: C7.2, R12.2, U3.1, U3.23
FILAMENT-: C8.2, R13.2, U3.16, U3.17
GND: C1.2, C2.2, C4.2, C5.2, C6.2, C9.2, C10.2, D2.2, R2.1, R6.2, R9.2, U1.2, U2.7, U4.14
unnamed: C3.1, R2.2, R3.2, U1.3
unnamed: C4.1, R8.1, U2.4
unnamed: C5.1, U2.2
unnamed: C7.1, R10.1
unnamed: C8.1, R11.1
unnamed: C10.1, D2.1, R12.1, R13.1
unnamed: D1.2, L1.2, U1.1
unnamed: R3.1, R4.2
unnamed: R5.2, R6.1, R7.2, U2.3
unnamed: R7.1, R8.2, R10.2, U2.5
unnamed: R11.2, U2.8
